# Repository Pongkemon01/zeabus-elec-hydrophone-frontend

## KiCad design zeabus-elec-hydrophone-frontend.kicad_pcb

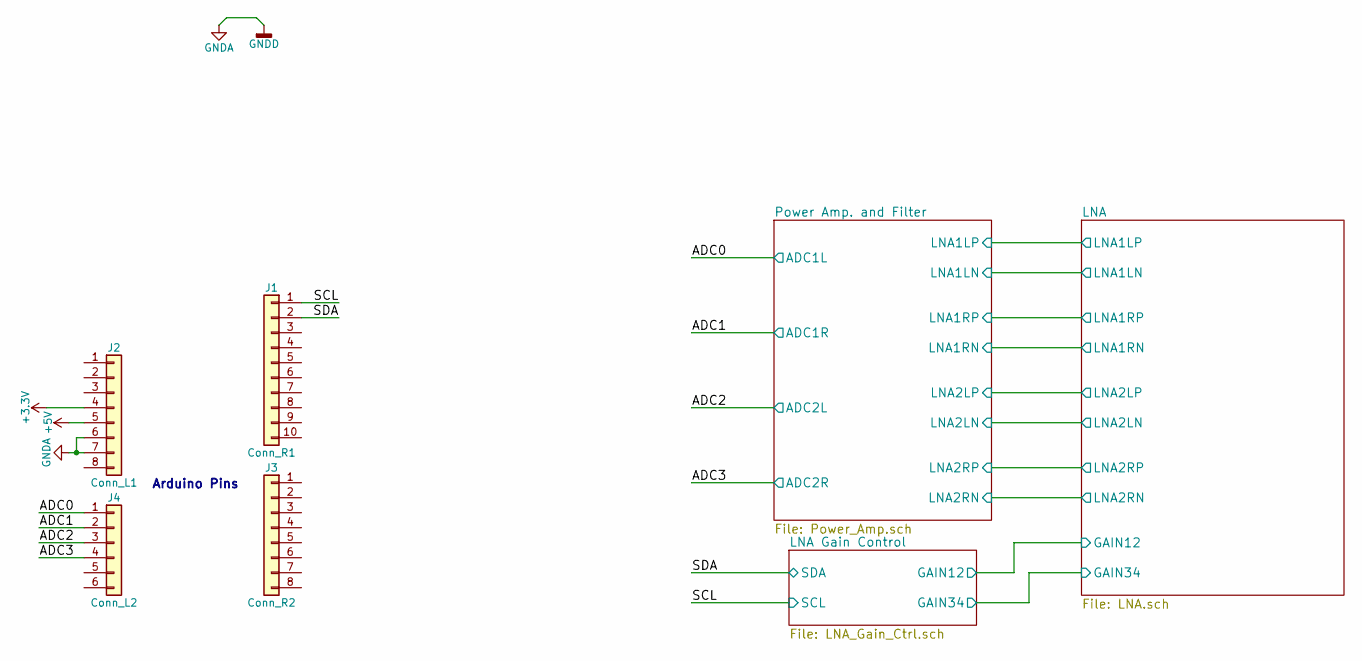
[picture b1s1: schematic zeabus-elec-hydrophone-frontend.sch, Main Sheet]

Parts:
J1: Conn_R1; Pin_Header_Straight_1x10_Pitch2.54mm
J2: Conn_L1; Pin_Header_Straight_1x08_Pitch2.54mm
J3: Conn_R2; Pin_Header_Straight_1x08_Pitch2.54mm
J4: Conn_L2; Pin_Header_Straight_1x06_Pitch2.54mm

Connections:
+3V3: J2.4; also elsewhere on the board
+5V: J2.5; also elsewhere on the board
/ADC0: J4.1; also elsewhere on the board
/ADC1: J4.2; also elsewhere on the board
/ADC2: J4.3; also elsewhere on the board
/ADC3: J4.4; also elsewhere on the board
/SCL: J1.1; also elsewhere on the board
/SDA: J1.2; also elsewhere on the board
GNDA: J2.6, J2.7; also elsewhere on the board

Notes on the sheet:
Arduino Pins

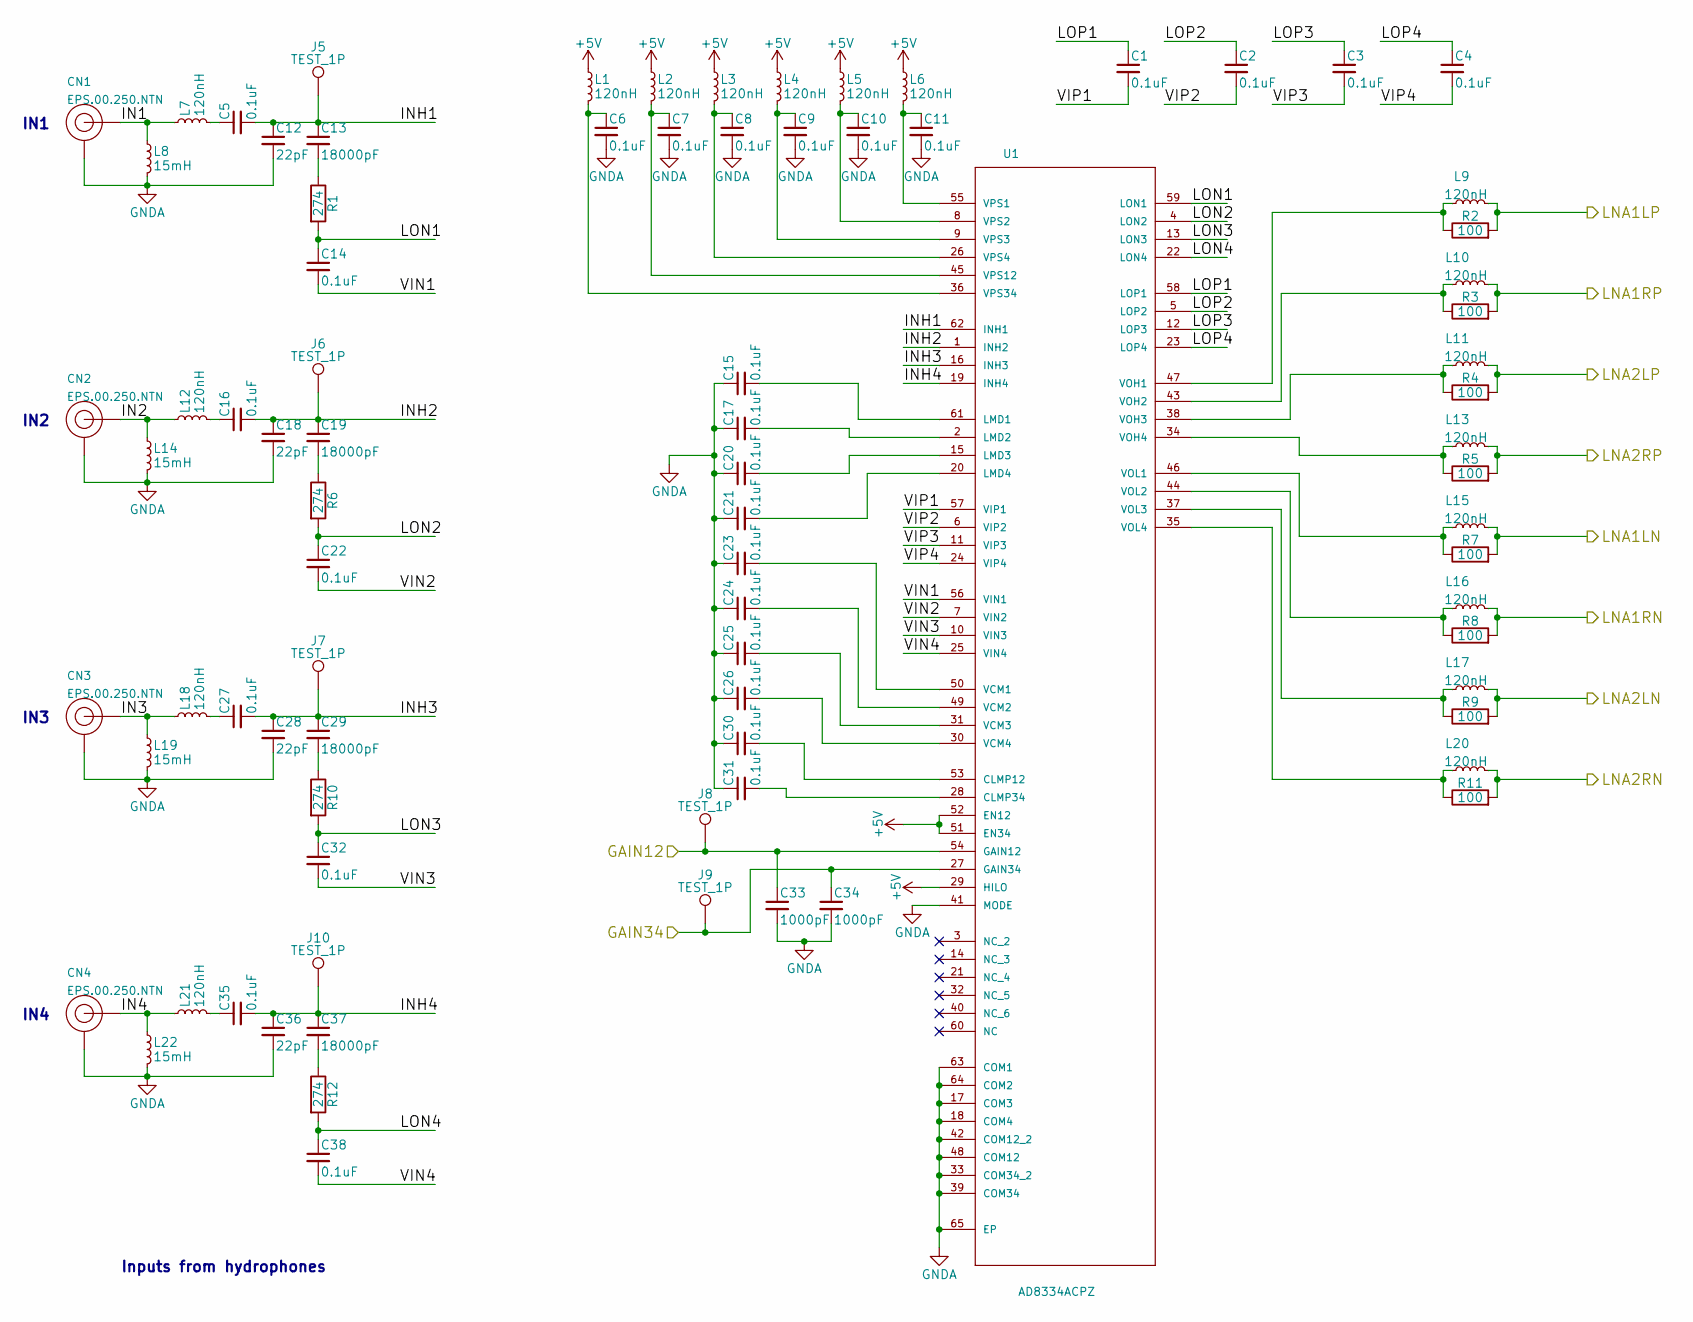
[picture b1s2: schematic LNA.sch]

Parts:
C1, C2, C3, C4, C5, C6, C7, C8, C9, C10, C11, C14, C15, C16, C17, C20, C21, C22, C23, C24, C25, C26, C27, C30, C31, C32, C35, C38: 0.1uF; C_0603_HandSoldering
C12, C18, C28, C36: 22pF; C_0603_HandSoldering
C13, C19, C29, C37: 18000pF; C_0603_HandSoldering
C33, C34: 1000pF; C_0603_HandSoldering
CN1, CN2, CN3, CN4: EPS.00.250.NTN; EPS-00-250
J5, J6, J7, J8, J9, J10: TEST_1P; Pin_Header_Straight_1x01_Pitch2.54mm
L1, L2, L3, L4, L5, L6, L7, L9, L10, L11, L12, L13, L15, L16, L17, L18, L20, L21: 120nH; L_0603_HandSoldering
L8, L14, L19, L22: 15mH; L-SDR0503
R1, R6, R10, R12: 274; R_0603_HandSoldering
R2, R3, R4, R5, R7, R8, R9, R11: 100; R_0603_HandSoldering
U1: AD8334ACPZ; QFN50P900X900X100-65N

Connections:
+5V: L1.1, L2.1, L3.1, L4.1, L5.1, L6.1, U1.29 (HILO), U1.51 (EN34), U1.52 (EN12); also elsewhere on the board
/LNA Gain Control/GAIN12: C33.1, J8.1, U1.54 (GAIN12); also elsewhere on the board
/LNA Gain Control/GAIN34: C34.1, J9.1, U1.27 (GAIN34); also elsewhere on the board
/LNA/IN1: CN1.1 (OUT), L7.1, L8.1
/LNA/IN2: CN2.1 (OUT), L12.1, L14.1
/LNA/IN3: CN3.1 (OUT), L18.1, L19.1
/LNA/IN4: CN4.1 (OUT), L21.1, L22.1
/LNA/INH1: C5.2, C12.1, C13.1, J5.1, U1.62 (INH1)
/LNA/INH2: C16.2, C18.1, C19.1, J6.1, U1.1 (INH2)
/LNA/INH3: C27.2, C28.1, C29.1, J7.1, U1.16 (INH3)
/LNA/INH4: C35.2, C36.1, C37.1, J10.1, U1.19 (INH4)
/LNA/LNA1LN: L15.2, R7.2; also elsewhere on the board
/LNA/LNA1LP: L9.2, R2.2; also elsewhere on the board
/LNA/LNA1RN: L16.2, R8.2; also elsewhere on the board
/LNA/LNA1RP: L10.2, R3.2; also elsewhere on the board
/LNA/LNA2LN: L17.2, R9.2; also elsewhere on the board
/LNA/LNA2LP: L11.2, R4.2; also elsewhere on the board
/LNA/LNA2RN: L20.2, R11.2; also elsewhere on the board
/LNA/LNA2RP: L13.2, R5.2; also elsewhere on the board
/LNA/LON1: C14.1, R1.2, U1.59 (LON1)
/LNA/LON2: C22.1, R6.2, U1.4 (LON2)
/LNA/LON3: C32.1, R10.2, U1.13 (LON3)
/LNA/LON4: C38.1, R12.2, U1.22 (LON4)
/LNA/LOP1: C1.1, U1.58 (LOP1)
/LNA/LOP2: C2.1, U1.5 (LOP2)
/LNA/LOP3: C3.1, U1.12 (LOP3)
/LNA/LOP4: C4.1, U1.23 (LOP4)
/LNA/VIN1: C14.2, U1.56 (VIN1)
/LNA/VIN2: C22.2, U1.7 (VIN2)
/LNA/VIN3: C32.2, U1.10 (VIN3)
/LNA/VIN4: C38.2, U1.25 (VIN4)
/LNA/VIP1: C1.2, U1.57 (VIP1)
/LNA/VIP2: C2.2, U1.6 (VIP2)
/LNA/VIP3: C3.2, U1.11 (VIP3)
/LNA/VIP4: C4.2, U1.24 (VIP4)
GNDA: C6.2, C7.2, C8.2, C9.2, C10.2, C11.2, C12.2, C15.1, C17.1, C18.2, C20.1, C21.1, C23.1, C24.1, C25.1, C26.1, C28.2, C30.1, C31.1, C33.2, C34.2, C36.2, CN1.2 (GND), CN1.3 (GND), CN1.4 (GND), CN1.5 (GND), CN2.2 (GND), CN2.3 (GND), CN2.4 (GND), CN2.5 (GND), CN3.2 (GND), CN3.3 (GND), CN3.4 (GND), CN3.5 (GND), CN4.2 (GND), CN4.3 (GND), CN4.4 (GND), CN4.5 (GND), L8.2, L14.2, L19.2, L22.2, U1.17 (COM3), U1.18 (COM4), U1.33 (COM34_2), U1.39 (COM34), U1.41 (MODE), U1.42 (COM12_2), U1.48 (COM12), U1.63 (COM1), U1.64 (COM2), U1.65 (EP); also elsewhere on the board
unnamed: C5.1, L7.2
unnamed: C6.1, L1.2, U1.36 (VPS34)
unnamed: C7.1, L2.2, U1.45 (VPS12)
unnamed: C8.1, L3.2, U1.26 (VPS4)
unnamed: C9.1, L4.2, U1.9 (VPS3)
unnamed: C10.1, L5.2, U1.8 (VPS2)
unnamed: C11.1, L6.2, U1.55 (VPS1)
unnamed: C13.2, R1.1
unnamed: C15.2, U1.61 (LMD1)
unnamed: C16.1, L12.2
unnamed: C17.2, U1.2 (LMD2)
unnamed: C19.2, R6.1
unnamed: C20.2, U1.15 (LMD3)
unnamed: C21.2, U1.20 (LMD4)
unnamed: C23.2, U1.50 (VCM1)
unnamed: C24.2, U1.49 (VCM2)
unnamed: C25.2, U1.31 (VCM3)
unnamed: C26.2, U1.30 (VCM4)
unnamed: C27.1, L18.2
unnamed: C29.2, R10.1
unnamed: C30.2, U1.53 (CLMP12)
unnamed: C31.2, U1.28 (CLMP34)
unnamed: C35.1, L21.2
unnamed: C37.2, R12.1
unnamed: L9.1, R2.1, U1.47 (VOH1)
unnamed: L10.1, R3.1, U1.43 (VOH2)
unnamed: L11.1, R4.1, U1.38 (VOH3)
unnamed: L13.1, R5.1, U1.34 (VOH4)
unnamed: L15.1, R7.1, U1.46 (VOL1)
unnamed: L16.1, R8.1, U1.44 (VOL2)
unnamed: L17.1, R9.1, U1.37 (VOL3)
unnamed: L20.1, R11.1, U1.35 (VOL4)

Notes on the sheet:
IN1
IN2
IN3
IN4
Inputs from hydrophones

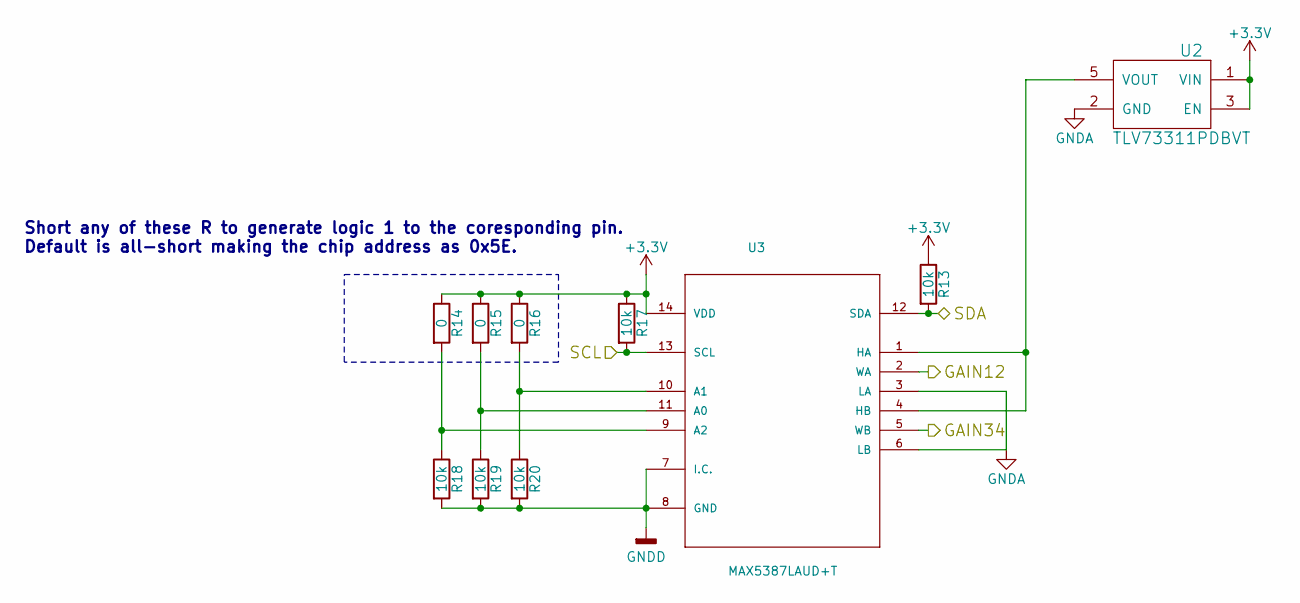
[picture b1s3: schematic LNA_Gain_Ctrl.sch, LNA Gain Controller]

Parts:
R13, R17, R18, R19, R20: 10k; R_0603_HandSoldering
R14, R15, R16: 0; R_0603_HandSoldering
U2: TLV73311PDBVT; SOT-23-5
U3: MAX5387LAUD+T; TSSOP-14_4.4x5mm_Pitch0.65mm

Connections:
+3V3: R13.1, R14.1, R15.1, R16.1, R17.1, U2.1 (VIN), U2.3 (EN), U3.14 (VDD); also elsewhere on the board
/LNA Gain Control/GAIN12: U3.2 (WA); also elsewhere on the board
/LNA Gain Control/GAIN34: U3.5 (WB); also elsewhere on the board
/SCL: R17.2, U3.13 (SCL); also elsewhere on the board
/SDA: R13.2, U3.12 (SDA); also elsewhere on the board
GNDA: R18.2, R19.2, R20.2, U2.2 (GND), U3.3 (LA), U3.6 (LB), U3.7 (I.C.), U3.8 (GND); also elsewhere on the board
unnamed: R14.2, R18.1, U3.9 (A2)
unnamed: R15.2, R19.1, U3.11 (A0)
unnamed: R16.2, R20.1, U3.10 (A1)
unnamed: U2.5 (VOUT), U3.1 (HA), U3.4 (HB)

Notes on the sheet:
Short any of these R to generate logic 1 to the coresponding pin. Default is all-short making the chip address as 0x5E.

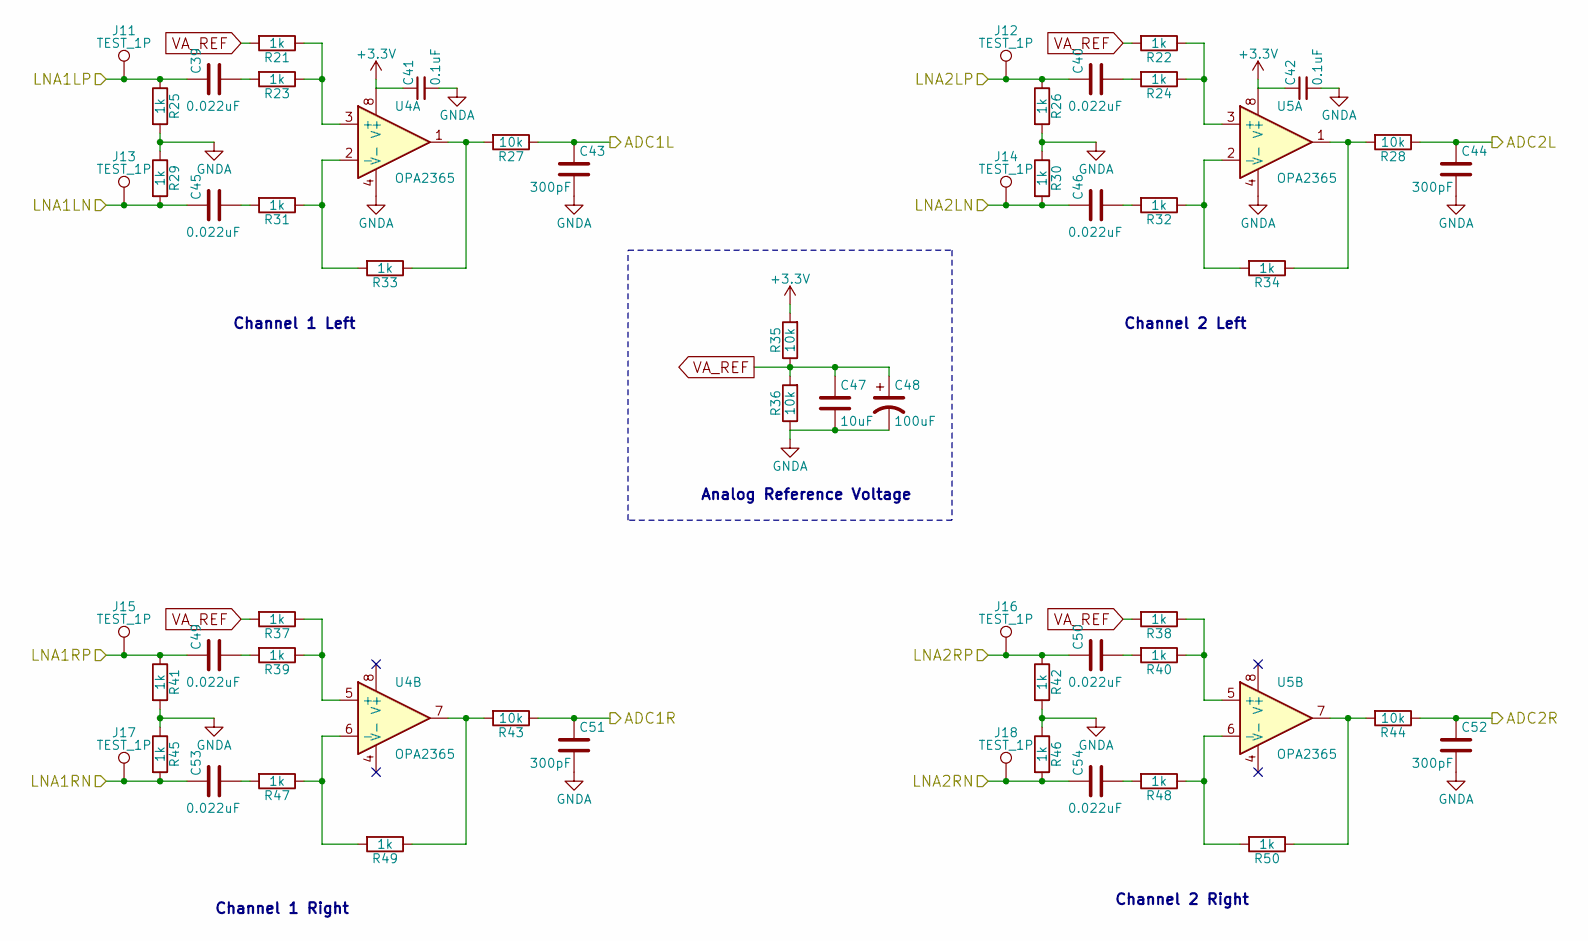
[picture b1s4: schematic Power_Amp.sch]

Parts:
C39, C40, C45, C46, C49, C50, C53, C54: 0.022uF; C_0603_HandSoldering
C41, C42: 0.1uF; C_0603_HandSoldering
C43, C44, C51, C52: 300pF; C_0603_HandSoldering
C47: 10uF; C_0805_HandSoldering
C48: 100uF; C_1210_HandSoldering
J11, J12, J13, J14, J15, J16, J17, J18: TEST_1P; Pin_Header_Straight_1x01_Pitch2.54mm
R21, R22, R23, R24, R25, R26, R29, R30, R31, R32, R33, R34, R37, R38, R39, R40, R41, R42, R45, R46, R47, R48, R49, R50: 1k; R_0603_HandSoldering
R27, R28, R35, R36, R43, R44: 10k; R_0603_HandSoldering
U4, U5: OPA2365; SOIC-8_3.9x4.9mm_Pitch1.27mm

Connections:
+3V3: C41.1, C42.1, R35.2, U4.8 (V+), U5.8 (V+); also elsewhere on the board
/ADC0: C43.1, R27.1; also elsewhere on the board
/ADC1: C51.1, R43.1; also elsewhere on the board
/ADC2: C44.1, R28.1; also elsewhere on the board
/ADC3: C52.1, R44.1; also elsewhere on the board
/LNA/LNA1LN: C45.1, J13.1, R29.2; also elsewhere on the board
/LNA/LNA1LP: C39.1, J11.1, R25.1; also elsewhere on the board
/LNA/LNA1RN: C53.1, J17.1, R45.2; also elsewhere on the board
/LNA/LNA1RP: C49.1, J15.1, R41.1; also elsewhere on the board
/LNA/LNA2LN: C46.1, J14.1, R30.2; also elsewhere on the board
/LNA/LNA2LP: C40.1, J12.1, R26.1; also elsewhere on the board
/LNA/LNA2RN: C54.1, J18.1, R46.2; also elsewhere on the board
/LNA/LNA2RP: C50.1, J16.1, R42.1; also elsewhere on the board
GNDA: C41.2, C42.2, C43.2, C44.2, C47.2, C48.2, C51.2, C52.2, R25.2, R26.2, R29.1, R30.1, R36.1, R41.2, R42.2, R45.1, R46.1, U4.4 (V-), U5.4 (V-); also elsewhere on the board
unnamed: C39.2, R23.2
unnamed: C40.2, R24.2
unnamed: C45.2, R31.2
unnamed: C46.2, R32.2
unnamed: C49.2, R39.2
unnamed: C50.2, R40.2
unnamed: C53.2, R47.2
unnamed: C54.2, R48.2
unnamed: R21.1, R23.1, U4.3 (+)
unnamed: R22.1, R24.1, U5.3 (+)
unnamed: R27.2, R33.1, U4.1
unnamed: R28.2, R34.1, U5.1
unnamed: R31.1, R33.2, U4.2 (-)
unnamed: R32.1, R34.2, U5.2 (-)
unnamed: R37.1, R39.1, U4.5 (+)
unnamed: R38.1, R40.1, U5.5 (+)
unnamed: R43.2, R49.1, U4.7
unnamed: R44.2, R50.1, U5.7
unnamed: R47.1, R49.2, U4.6 (-)
unnamed: R48.1, R50.2, U5.6 (-)
VA_REF: C47.1, C48.1, R21.2, R22.2, R35.1, R36.2, R37.2, R38.2

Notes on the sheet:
Analog Reference Voltage
Channel 1 Left
Channel 1 Right
Channel 2 Left
Channel 2 Right

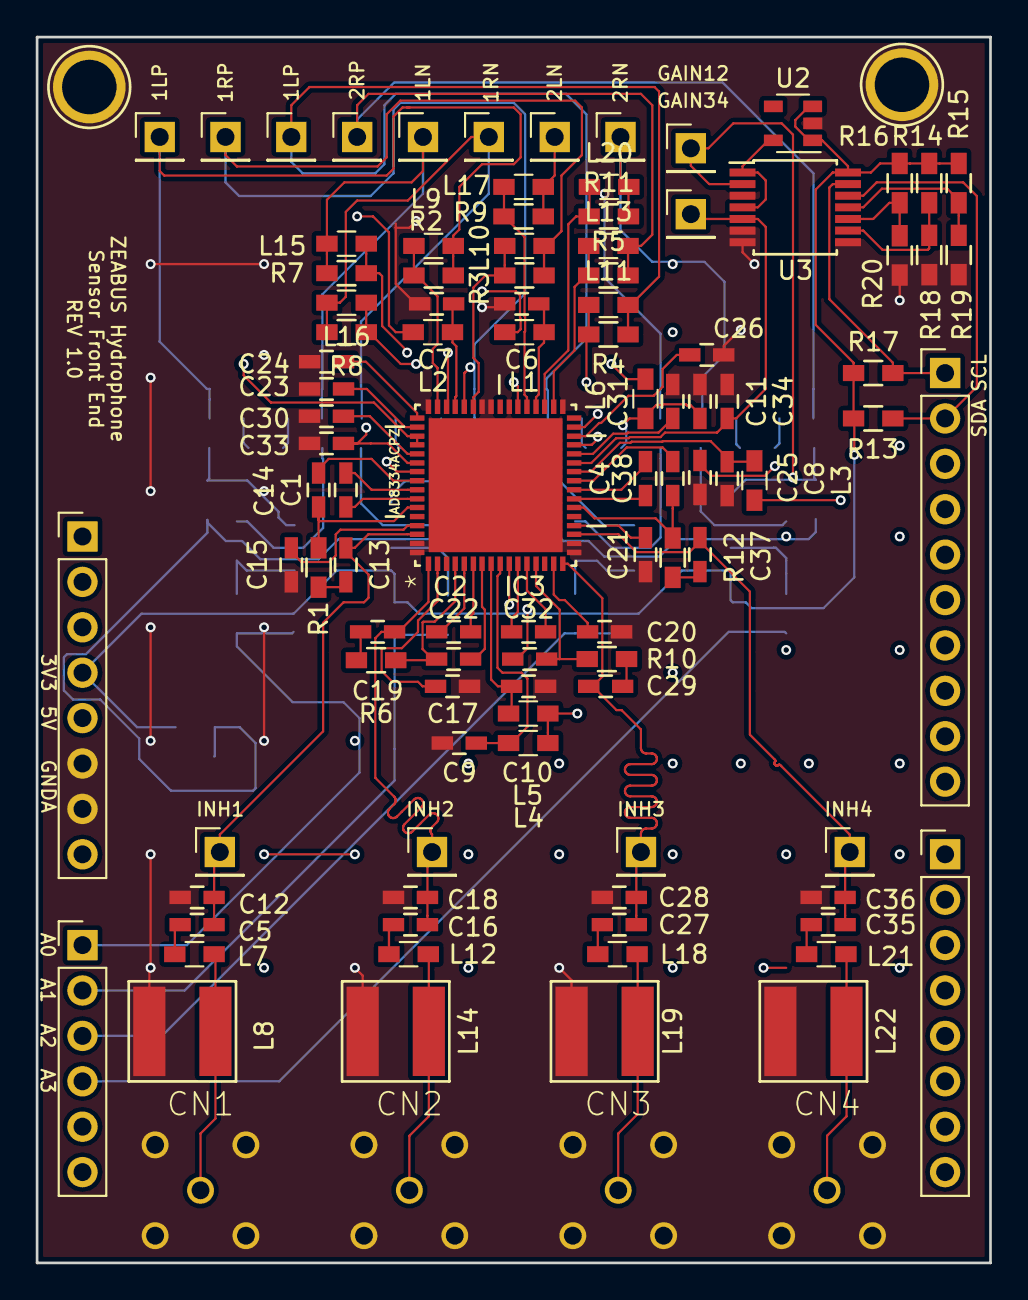
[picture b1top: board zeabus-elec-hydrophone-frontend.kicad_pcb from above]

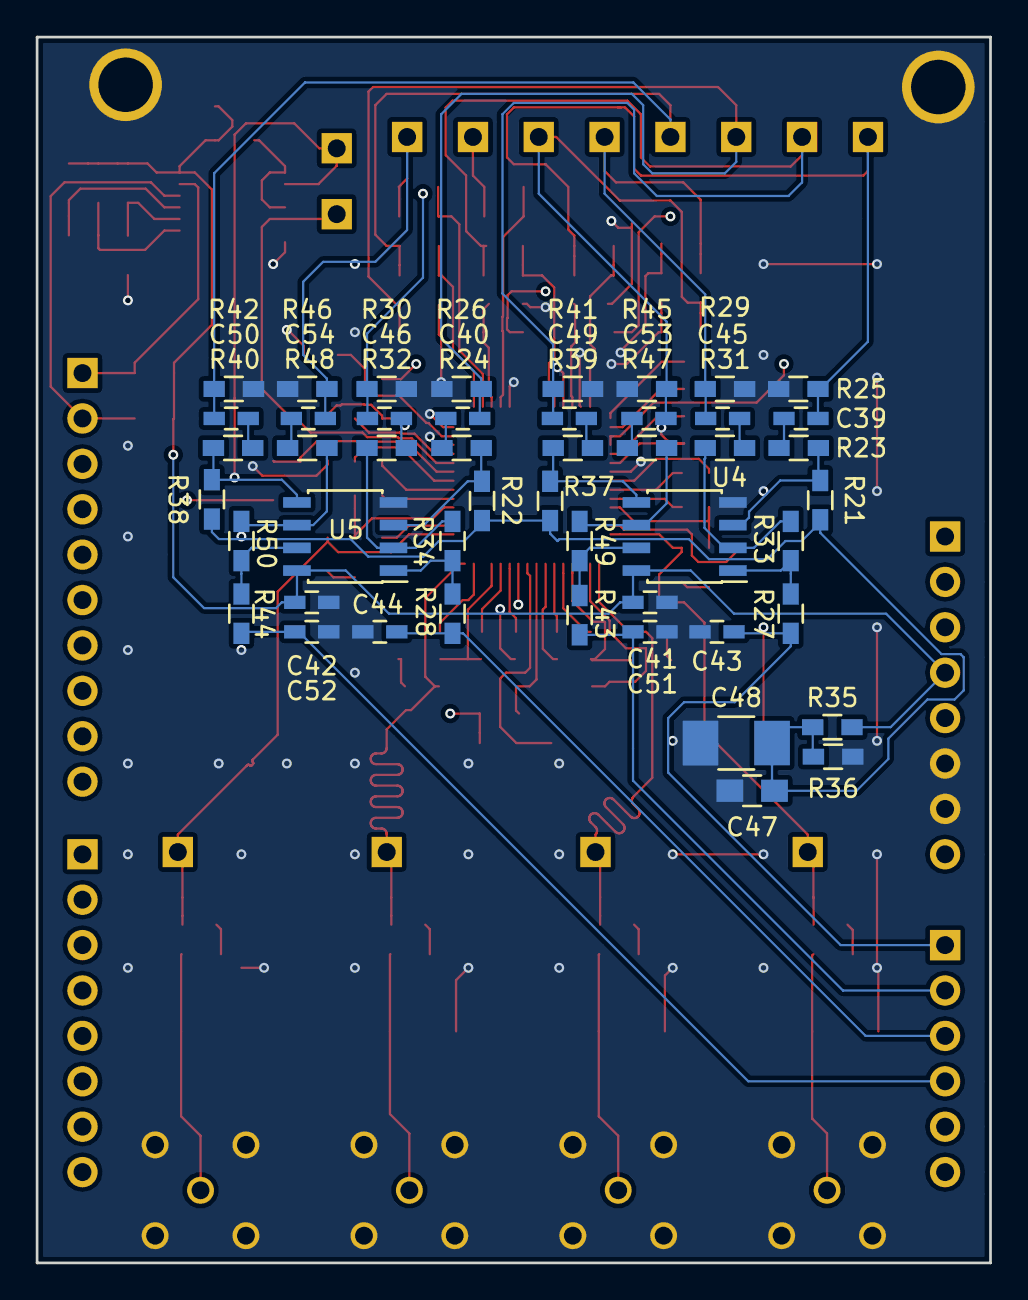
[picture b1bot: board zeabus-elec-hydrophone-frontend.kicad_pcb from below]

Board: 4 copper layers, 53.3 x 68.6 mm, 153 parts (48 on the bottom side), 100 nets.

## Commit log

2018-04-19 First commit with schematic
2018-04-19 Change OPAMP number to OPA2365
2018-04-22 Bug fixed 1
2018-04-22 add LNA Gain Test Point
2018-04-22 add BOM file
2018-04-22 Assigned footprint for dimension checking
2018-04-27 First released
2018-04-28 edit layout and silkscreen
2018-04-28 Finished the PCB plus adding some stitching vias
2018-04-28 add gerber file and sent to pcbway
2018-11-20 Add simulation file
2019-01-30 Update simulation for high-gain version
2019-10-29 Project closed
